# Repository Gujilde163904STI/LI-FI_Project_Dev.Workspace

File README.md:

# ⚡️ LIFI-PROJECT

> A modular development workspace for a **Light Fidelity (LI-FI)** embedded system powered by **Raspberry Pi 3**, **Raspberry Pi 4**, and **ESP8266**, featuring independent flashing workflows, photodiode-based TCP/IP transmission, a Firebase dashboard, and AI-assisted diagnostics.

---

## 📡 Project Overview

This project enables **data transmission via light** using photodiodes and embedded devices, simulating TCP/IP or Wi-Fi-like packet exchange between Raspberry Pi units and ESP8266 microcontrollers. Each device is programmed independently and auto-connects on boot without runtime setup.

- 🔦 **LI-FI Protocol** using light to transmit IP/data
- 🧱 **Modular build system** for RPi3, RPi4, and ESP8266
- 🌐 **Firebase-powered** real-time dashboard (logs, configs, flash jobs)
- 🤖 **AI-assisted debugging** using Gemini and Mistral (LM Studio)
- 🔒 **Offline-capable flashing** with precompiled scripts and auto-connection
- 🧪 **Simulations** using Wokwi and custom protocol testbeds

---

## 📁 Project Structure

LI-FI_Project_Dev.Workspace/
├── RPI3/                  # Raspberry Pi 3 firmware & configs
├── RPI4/                  # Raspberry Pi 4 firmware & configs
├── FLASH_8266/            # NodeMCU ESP8266 firmware & scripts
├── firebase-dashboard/    # Firebase Hosting frontend (JS/HTML)
├── tools/                 # Arduino-CLI, PlatformIO, and flash tools
├── scripts/               # Shell/CLI scripts for automation
├── simulation-workspace/  # Wokwi builds & virtual tests
├── docs/                  # Documentation, wiring, protocol guides
├── integrations/          # IOTStack, MQTT libs, esp-idf tools
├── resources/             # Markdown, config presets, JSON schemas

---

## 🚀 Features

### 🔧 Embedded System Logic
- 📦 Independently flashable modules: RPi3, RPi4, ESP8266
- 🧠 AI-based assistant (`Junie`, `Gemini`, `Cursor`, `Mistral`) for code generation
- 🔄 Serial/TCP messaging over photodiode channels
- 📂 Organized workspace for firmware, simulation, and flashing

### 📊 Firebase Integration
- 🔥 Firestore schema for device logs, flash jobs, configs, and status
- 🛠️ Firebase Hosting with dark violet console UI
- 🧪 Secure rules: Admin-only writes, public authenticated reads
- 📈 Live signal monitoring and device flash tracking

### 🧠 AI Tools
- 🎨 Diagramming: Mermaid, Excalidraw, or Tldraw
- 💡 Debugging: Gemini prompts based on historical logs
- 🤖 Model support: Mistral 22B (`LM Studio`), Gemini 1.5 Pro, GPT-4.5

---

## 🛠️ Requirements

| Tool                | Version / Note                    |
|---------------------|-----------------------------------|
| Node.js             | >= 18.x                           |
| Firebase CLI        | `npm install -g firebase-tools`   |
| Arduino-CLI / PIO   | Included in `/tools/`             |
| Python 3.x          | For RPi build scripts             |
| LM Studio (optional)| `codestral-22b-v0.1`              |

---

## 🔥 Firebase Setup

1. Connect your VSCode terminal:
   ```bash
   firebase login
   firebase use --add

2.	Initialize Hosting & Firestore:
   
   firebase init
  	
4.	Deploy:

   firebase deploy

🧪 Flash Workflow (ESP/RPi)

# Build + Flash ESP8266
cd FLASH_8266/
python3 flash_esp8266.py --target=nodeMCUv3

# Build Raspberry Pi 3 Firmware
cd RPI3/
python3 build.py --target=rpi3 --flash

# Build Raspberry Pi 4 Firmware
cd RPI4/
python3 build.py --target=rpi4 --flash

💻 Firebase Dashboard

Hosted live at:
https://studio--lifi-embedded-console.us-central1.hosted.app/dashboard

OR locally:

bash
firebase emulators:start

Features:
	•	🔍 View RPi/ESP logs, signal, and flash status
	•	📡 Configure devices from the browser
	•	🔐 Admin login with role-based Firestore rules

⸻

🎨 Style Guide

Element              Value
Primary Color        Gradient Dark & Light Violet
Background           Elegant Dark (#202A40)
Accent Color         Teal (#3EDBF0)
Fonts                Inter, Space Grotesk, Source Code Pro
Icons                Minimal vector-style, inline SVG
Theme Inspired       Prompt 3 App Icon + Firebase Studio

⸻

📌 TODO
	•	Auto-device registration on flash
	•	AI-powered log summarization in dashboard
	•	OTA update support for ESP8266
	•	Gemini + Firebase CLI helper integration

🧠 Prompt Examples (Gemini/GPT)

js
"Generate Firestore rules that allow only admins to write to /configs"
"Simulate 5 rpi3 logs with timestamps and errors"
"Connect ESP8266 to Firestore via REST"
"Deploy my Firebase app from CLI and trigger emulators"

-------------------------------------------------------
📜 License

This project is licensed under MIT License. See LICENSE for details.

⸻

🙌 Credits
	•	Developed by: Gian Carlo Gujilde
	•	Tools: Cursor, Gemini, LM Studio, Firebase, Arduino, Wokwi, ESP-IDF
	•	Core Models: codestral-22b-v0.1, Gemini Pro, GPT-4

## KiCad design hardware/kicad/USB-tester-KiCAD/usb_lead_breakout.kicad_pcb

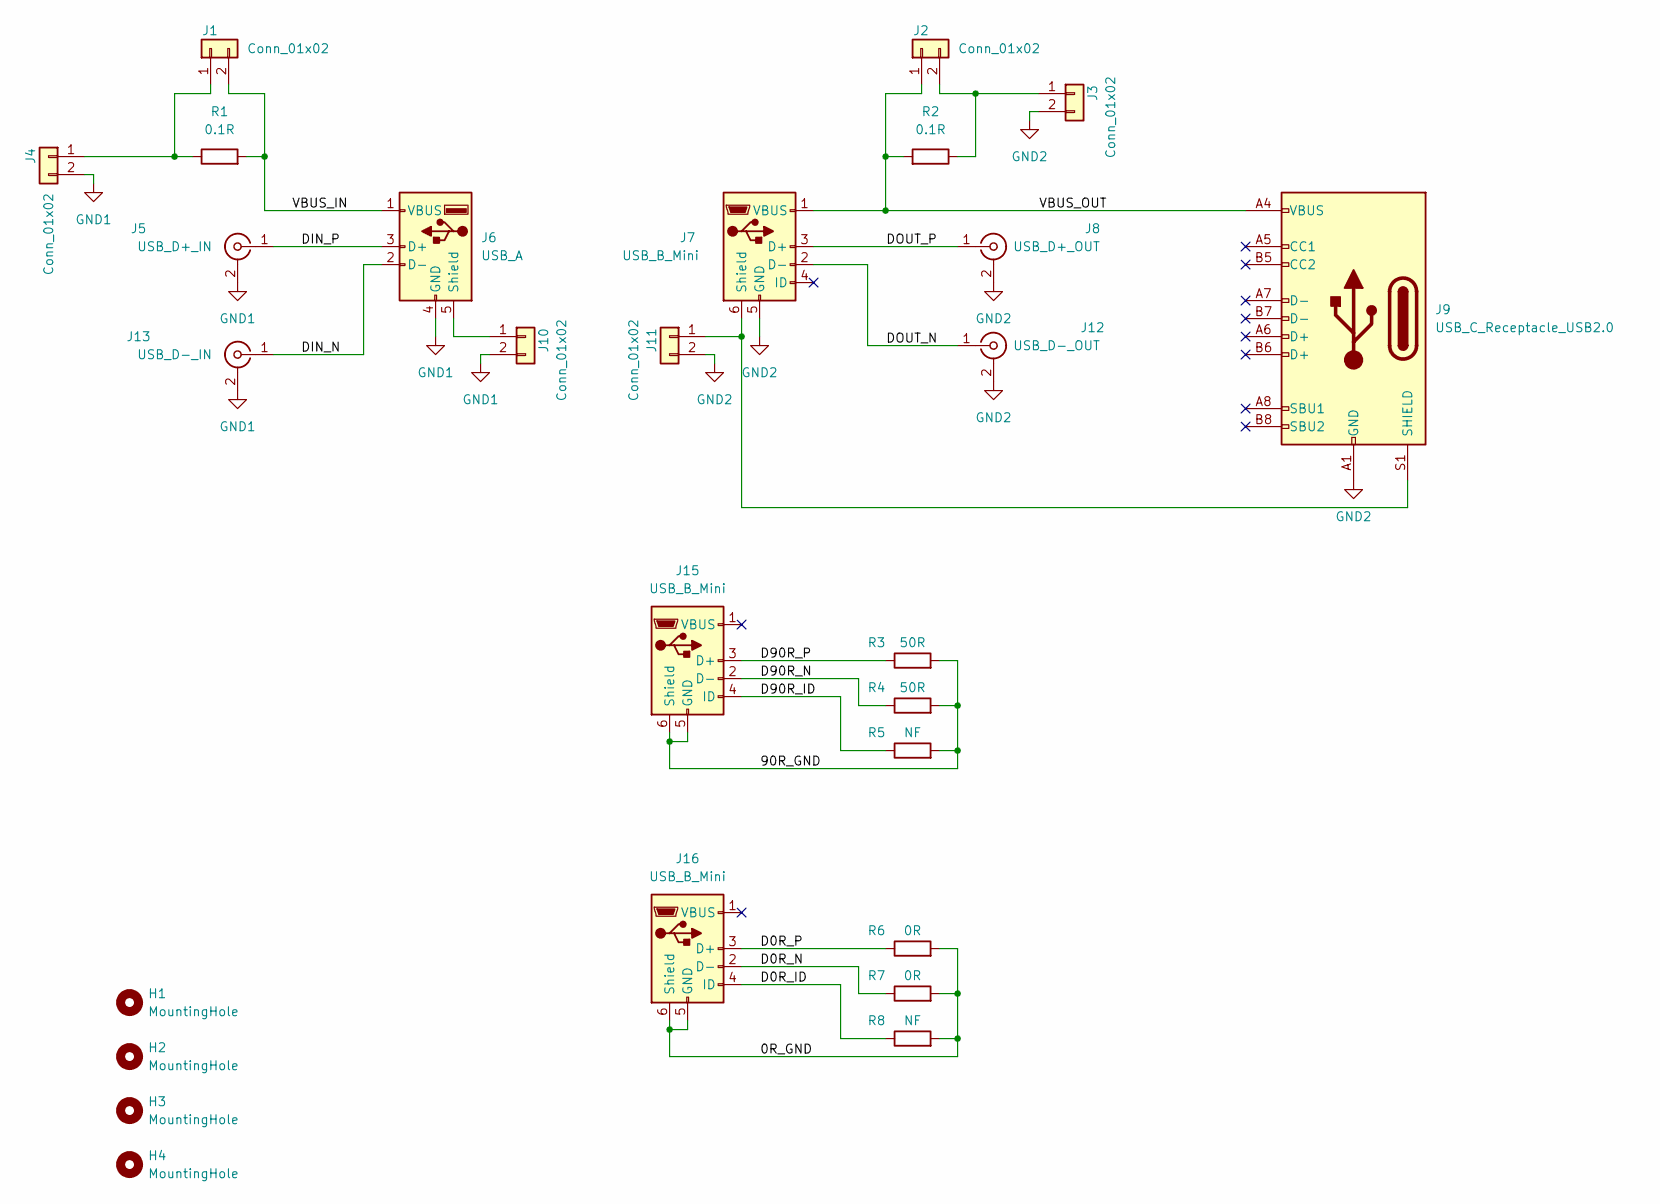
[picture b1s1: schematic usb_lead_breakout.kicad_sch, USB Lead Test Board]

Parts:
H1, H2, H3, H4: MountingHole; MountingHole_2.7mm_M2.5_ISO7380_Pad_TopBottom
J1, J2, J3, J4, J10, J11: Conn_01x02; PinHeader_1x02_P2.54mm_Vertical
J5: USB_D+_IN; SMA_Amphenol_132289_EdgeMount
J6: USB_A; USB_A_Molex_67643_Horizontal
J7, J15, J16: USB_B_Mini; USB_Micro-B_Molex-105017-0001
J8: USB_D+_OUT; SMA_Amphenol_132289_EdgeMount
J9: USB_C_Receptacle_USB2.0; USB_C_Receptacle_HRO_TYPE-C-31-M-12
J12: USB_D-_OUT; SMA_Amphenol_132289_EdgeMount
J13: USB_D-_IN; SMA_Amphenol_132289_EdgeMount
R1, R2: 0.1R; R_1206_3216Metric_Pad1.30x1.75mm_HandSolder
R3, R4: 50R; R_0402_1005Metric_Pad0.72x0.64mm_HandSolder
R5, R8: NF; R_0402_1005Metric_Pad0.72x0.64mm_HandSolder
R6, R7: 0R; R_0402_1005Metric_Pad0.72x0.64mm_HandSolder

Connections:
/0R_GND: J16.5 (GND), J16.6 (Shield), R6.2, R7.2, R8.2
/90R_GND: J15.5 (GND), J15.6 (Shield), R3.2, R4.2, R5.2
/D0R_ID: J16.4 (ID), R8.1
/D0R_N: J16.2 (D-), R7.1
/D0R_P: J16.3 (D+), R6.1
/D90R_ID: J15.4 (ID), R5.1
/D90R_N: J15.2 (D-), R4.1
/D90R_P: J15.3 (D+), R3.1
/DIN_N: J6.2 (D-), J13.1 (In)
/DIN_P: J5.1 (In), J6.3 (D+)
/DOUT_N: J7.2 (D-), J12.1 (In)
/DOUT_P: J7.3 (D+), J8.1 (In)
/VBUS_IN: J1.2, J6.1 (VBUS), R1.2
/VBUS_OUT: J2.1, J7.1 (VBUS), J9.A4 (VBUS), J9.A9 (VBUS), J9.B4 (VBUS), J9.B9 (VBUS), R2.2
GND1: J4.2, J5.2 (Ext), J6.4 (GND), J10.2, J13.2 (Ext)
GND2: J3.2, J7.5 (GND), J8.2 (Ext), J9.A1 (GND), J9.A12 (GND), J9.B1 (GND), J9.B12 (GND), J11.2, J12.2 (Ext)
unnamed: J1.1, J4.1, R1.1
unnamed: J2.2, J3.1, R2.1
unnamed: J6.5 (Shield), J10.1
unnamed: J7.6 (Shield), J9.S1 (SHIELD), J11.1

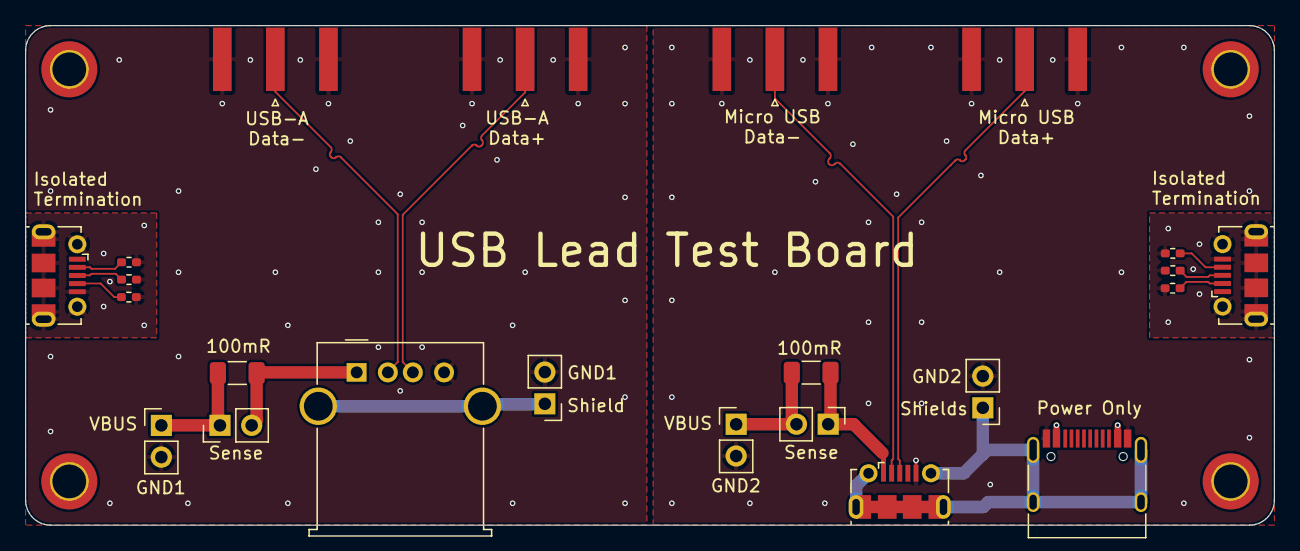
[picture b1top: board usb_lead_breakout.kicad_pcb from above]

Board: 4 copper layers, 100.0 x 40.0 mm, 27 parts (0 on the bottom side), 20 nets.

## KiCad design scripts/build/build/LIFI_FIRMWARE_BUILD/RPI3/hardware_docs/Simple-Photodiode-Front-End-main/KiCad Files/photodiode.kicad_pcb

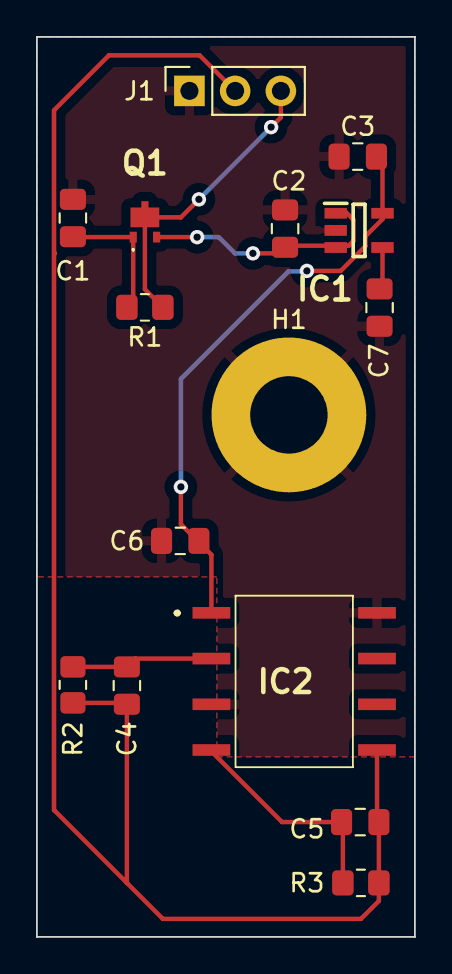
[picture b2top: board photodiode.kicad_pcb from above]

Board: 2 copper layers, 21.0 x 50.0 mm, 15 parts (0 on the bottom side), 9 nets.

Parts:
C1, C2, C3, C4, C5, C6, C7: C; C_0805_2012Metric_Pad1.18x1.45mm_HandSolder
H1: MountingHole_Pad; MountingHole_4.3mm_M4_Pad
IC1: TC1014-3.3VCT713; SOT95P280X145-5N
IC2: OPT101P-J; OPT101PJ
J1: Conn_01x03_Male; PinSocket_1x03_P2.54mm_Vertical
Q1: PBSS4360PAS-QX; PBSS4310PASQX
R1, R2, R3: R; R_0805_2012Metric_Pad1.20x1.40mm_HandSolder

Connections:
GNDREF: C1.1, C2.1, C3.1, C6.2, C7.1, H1.1, IC1.2 (GND), IC2.3 (-V), IC2.8 (COMMON), J1.1
unnamed: C1.2, Q1.1 (B), R1.2
unnamed: C2.2, IC1.1 (VIN), IC1.3 (~SHDN), Q1.2 (E)
unnamed: C3.2, C6.1, IC1.5 (VOUT), IC2.1 (VS)
unnamed: C4.2, IC2.2 (-IN), R2.2
unnamed: C5.2, IC2.4 (1MΩ_FEEDBACK), R3.2
unnamed: C7.2, IC1.4 (BYPASS)
unnamed: J1.3, Q1.3 (C_1), Q1.4 (C_2), R1.1
out: C4.1, C5.1, IC2.5 (OUTPUT), J1.2, R2.1, R3.1

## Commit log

2025-07-08 Apply perf optimizations & devcontainer
2025-07-08 Add development automation scripts
    - monitor-memory.sh: Provides memory/swap monitoring with threshold alerts
    - vscode-troubleshoot.sh: VS Code performance troubleshooting tools
    - weekly-updates.sh: Automated weekly update script for containers and extensions
2025-07-08 Initial Mac setup and configuration scripts
2025-07-08 LI-FI Mac setup: VS Code config, extension scripts, Git LFS, PAT auth
2025-07-08 LI-FI Mac setup complete
2025-07-08 Complete LI-FI setup: All configs, scripts, extensions ready for Windows sync
